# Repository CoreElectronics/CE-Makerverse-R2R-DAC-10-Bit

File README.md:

# Makerverse™ R2R DAC 10-Bit

This is the repo for the Core Electronics [Makerverse R2R DAC 10-Bit](https://core-electronics.com.au/catalog/product/view/sku/ce08391).

The PCB layout project requires KiCAD 6.0 or newer to view. The schematic is provided in PDF format in the Documents folder.

## License
This project is open source - please review the LICENSE.md file for further licensing information.

If you have any technical questions, or concerns about licensing, please contact technical support on the [Core Electronics forums](https://forum.core-electronics.com.au/).

*\"Makerverse\" and the Makerverse logo are trademarks of Core Electronics Pty Ltd.*

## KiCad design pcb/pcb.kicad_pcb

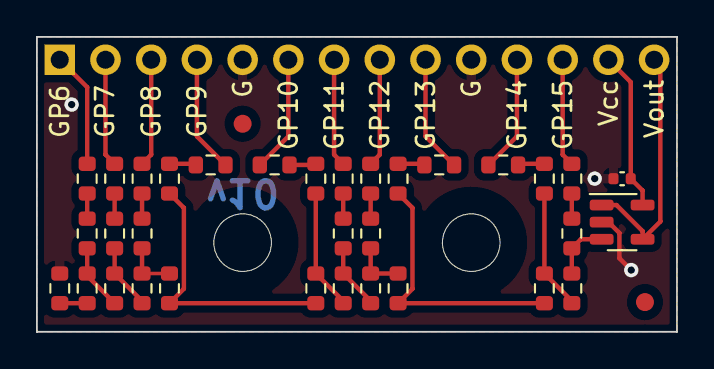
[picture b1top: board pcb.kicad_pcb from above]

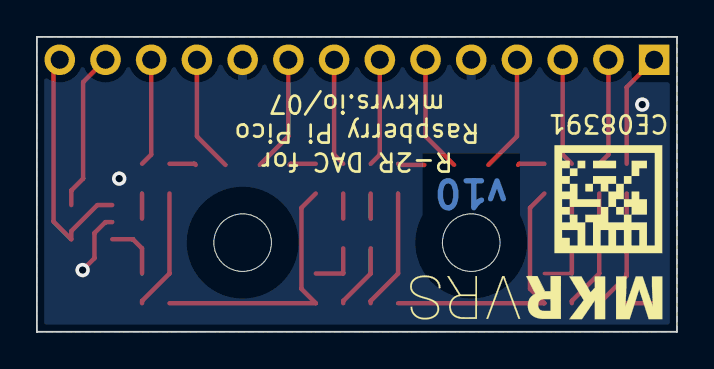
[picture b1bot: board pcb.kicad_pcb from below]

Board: 2 copper layers, 35.6 x 16.4 mm, 40 parts (2 on the bottom side), 34 nets.

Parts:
C1: 100nF; C_0402_1005Metric
FID1, FID2: Fiducial; Fiducial_1mm_Mask2mm
G1: Datamatrix; CE08391
G2: LOGO_Makerverse; makerverse_logo_short_14.0x2.4mm
H1, H2: MountingHole; MountingHole_3.2mm_M3
J1: Conn_01x14; PinHeader_1x14_P2.54mm_Vertical
R1, R2, R3, R4, R5, R6, R7, R8, R9, R10, R11, R12, R13, R14, R15, R16, R17, R18, R19, R20, R21, R22, R23, R24, R25, R26, R27, R28, R29, R30, R31: R; R_0603_1608Metric
U1: MCP6001-OT; SOT-23-5

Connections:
/D0: J1.1, R3.2
/D1: J1.2, R6.2
/D2: J1.3, R9.2
/D3: J1.4, R12.2
/D4: J1.6, R15.2
/D5: J1.7, R18.2
/D6: J1.8, R21.2
/D7: J1.9, R24.2
/D8: J1.11, R27.2
/D9: J1.12, R30.2
/Vout: J1.14, U1.1, U1.4 (-)
GND: C1.2, J1.5, J1.10, R1.1, U1.2 (V-)
unnamed: R1.2, R2.1
unnamed: R2.2, R4.1, R5.1
unnamed: R3.1, R4.2
unnamed: R5.2, R7.1, R8.1
unnamed: R6.1, R7.2
unnamed: R8.2, R10.1, R11.1
unnamed: R9.1, R10.2
unnamed: R11.2, R13.1, R14.1
unnamed: R12.1, R13.2
unnamed: R14.2, R16.1, R17.1
unnamed: R15.1, R16.2
unnamed: R17.2, R19.1, R20.1
unnamed: R18.1, R19.2
unnamed: R20.2, R22.1, R23.1
unnamed: R21.1, R22.2
unnamed: R23.2, R25.1, R26.1
unnamed: R24.1, R25.2
unnamed: R26.2, R28.1, R29.1
unnamed: R27.1, R28.2
unnamed: R29.2, R31.1, U1.3 (+)
unnamed: R30.1, R31.2
VCC: C1.1, J1.13, U1.5 (V+)

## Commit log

2022-06-14 Typo fix
